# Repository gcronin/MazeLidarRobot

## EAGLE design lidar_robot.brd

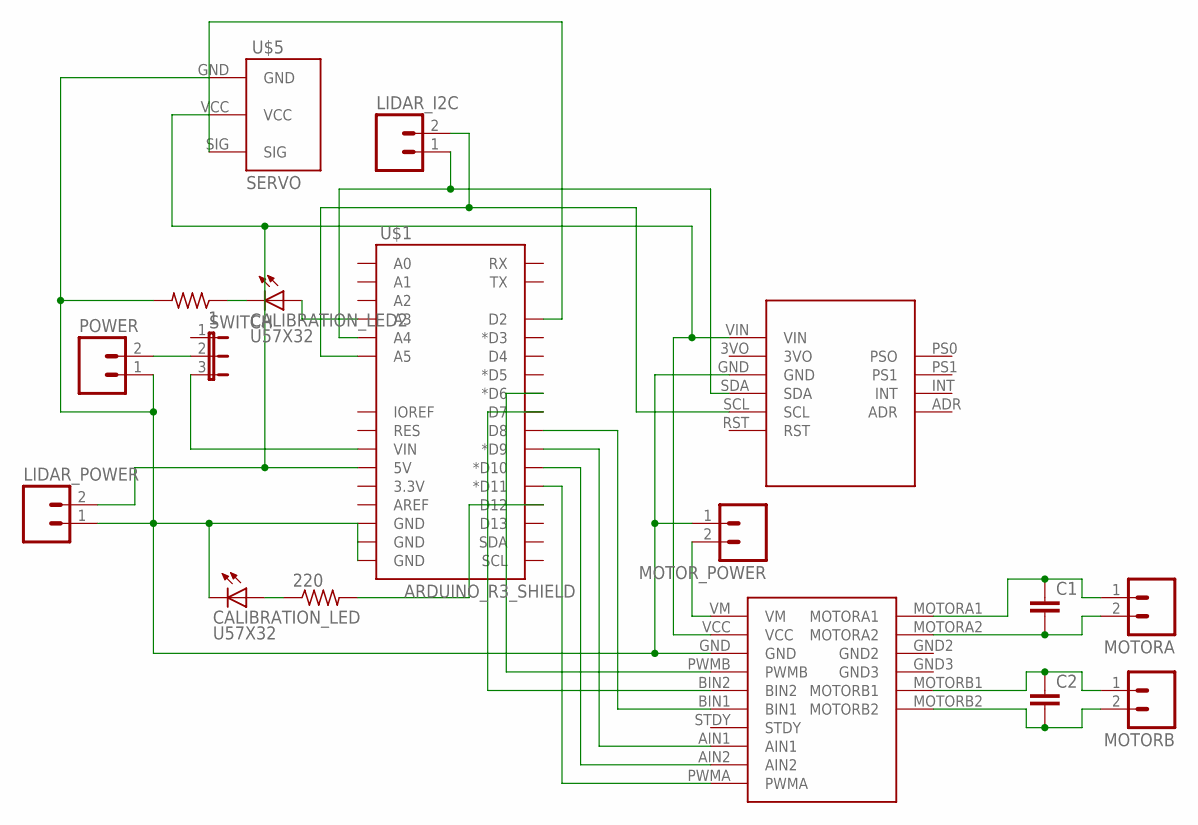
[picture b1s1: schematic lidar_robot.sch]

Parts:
1, 220: R-US_0207/10; 0207/10
C1, C2: C2.5/4; C2.5-4
CALIBRATION_LED, CALIBRATION_LED2: U57X32
LIDAR_I2C: M02LOCK; 1X02_LOCK
LIDAR_POWER: M02LOCK; 1X02_LOCK
MOTORA: M02LOCK; 1X02_LOCK
MOTORB: M02LOCK; 1X02_LOCK
MOTOR_POWER: M02LOCK; 1X02_LOCK
POWER: M02LOCK; 1X02_LOCK
SWITCH: JP2E; JP2
U$1: ARDUINO_R3_SHIELD; UNO_R3_SHIELD
U$2: BN0055
U$3: TB6612
U$5: SERVO

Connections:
unnamed: POWER.2, SWITCH.2
unnamed: SWITCH.3, U$1.VIN
unnamed: LIDAR_POWER.2, U$1.5V, U$2.VIN, U$3.VCC, U$5.VCC
unnamed: C2.1, MOTORB.1, U$3.MOTORB1
unnamed: C2.2, MOTORB.2, U$3.MOTORB2
unnamed: C1.1, MOTORA.1, U$3.MOTORA1
unnamed: C1.2, MOTORA.2, U$3.MOTORA2
unnamed: 1.2, CALIBRATION_LED.K (C), LIDAR_POWER.1, MOTOR_POWER.1, POWER.1, U$1.GND@0 (GND), U$1.GND@1 (GND), U$1.GND@2 (GND), U$2.GND, U$3.GND, U$5.GND
unnamed: U$1.D11 (*D11), U$3.PWMA
unnamed: U$1.D10 (*D10), U$3.AIN2
unnamed: LIDAR_I2C.1, U$1.A4, U$2.SDA
unnamed: LIDAR_I2C.2, U$1.A5, U$2.SCL
unnamed: U$1.D9 (*D9), U$3.AIN1
unnamed: U$1.D8, U$3.BIN1
unnamed: U$1.D2, U$5.SIG
unnamed: 220.2, U$1.D12
unnamed: U$1.D7, U$3.BIN2
unnamed: 220.1, CALIBRATION_LED.A
unnamed: U$1.D6 (*D6), U$3.PWMB
unnamed: 1.1, CALIBRATION_LED2.K (C)
unnamed: CALIBRATION_LED2.A, U$1.A3
unnamed: MOTOR_POWER.2, U$3.VM

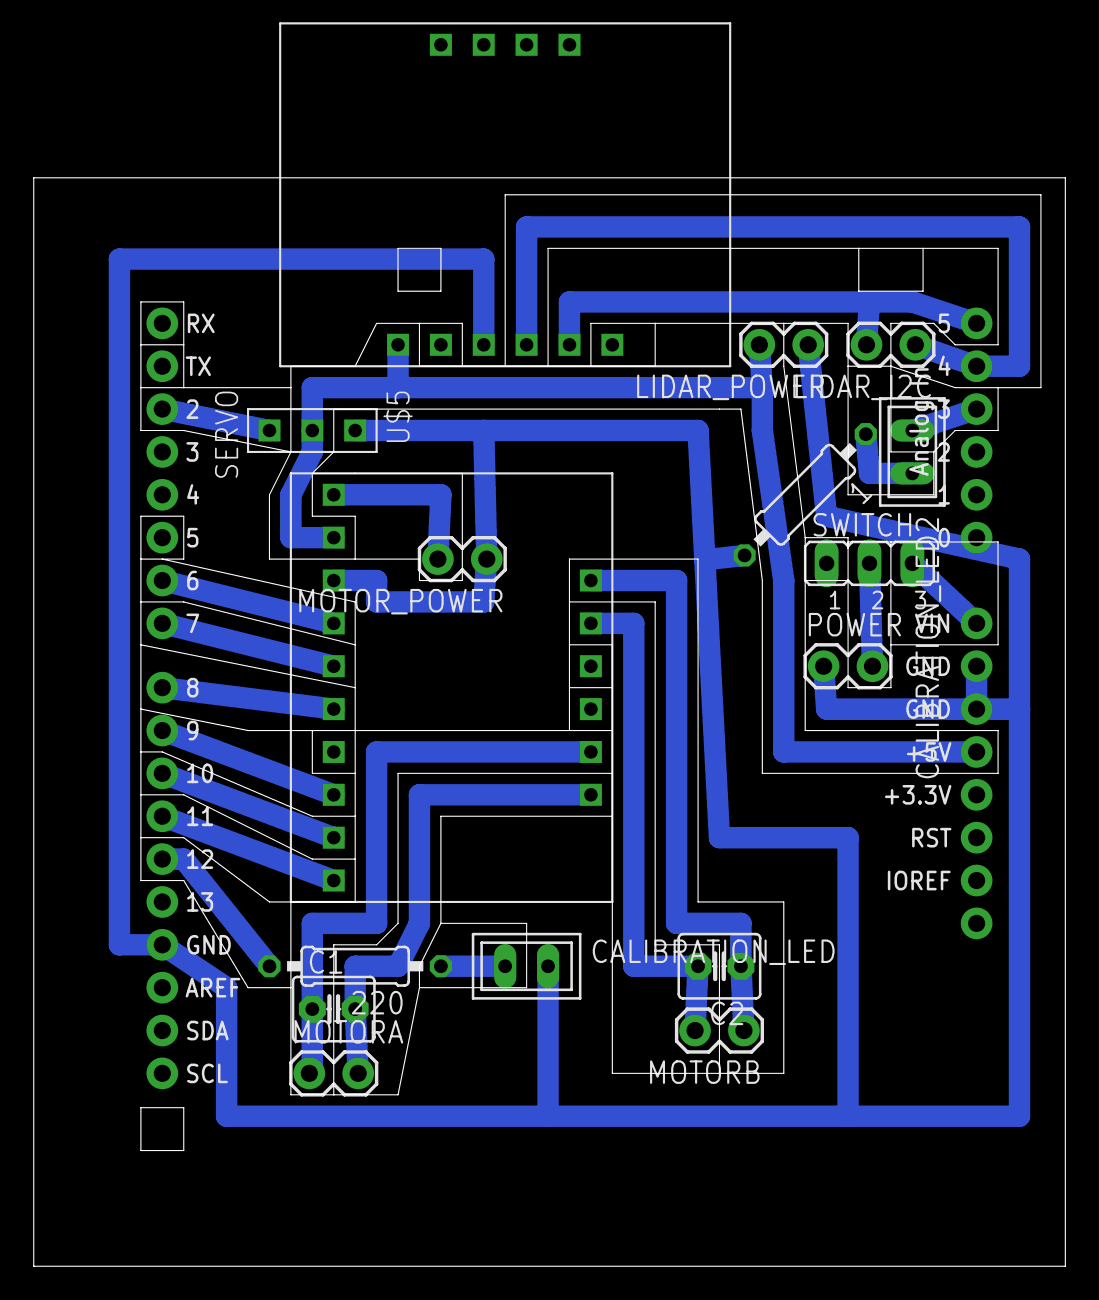
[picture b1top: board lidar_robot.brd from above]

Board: 2 copper layers, 61.1 x 64.5 mm, 17 parts (0 on the bottom side), 22 nets.

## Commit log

2017-02-01 :neckbeard: Added .gitattributes & .gitignore files
2017-02-01 Working Test Programs for Lidar and BN0055
2017-02-02 Tested Integrated Lidar and BN0055 with I2C.h Library
2017-03-06 PCB Board added, pins updated

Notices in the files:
parts and their libraries:
SparkFun: Licensing: CC v3.0 Share-Alike You are welcome to use this library for commercial purposes.
SparkFun-Boards: Licensing: Creative Commons ShareAlike 4.0 International - https://creativecommons.org/licenses/by-sa/4.0
